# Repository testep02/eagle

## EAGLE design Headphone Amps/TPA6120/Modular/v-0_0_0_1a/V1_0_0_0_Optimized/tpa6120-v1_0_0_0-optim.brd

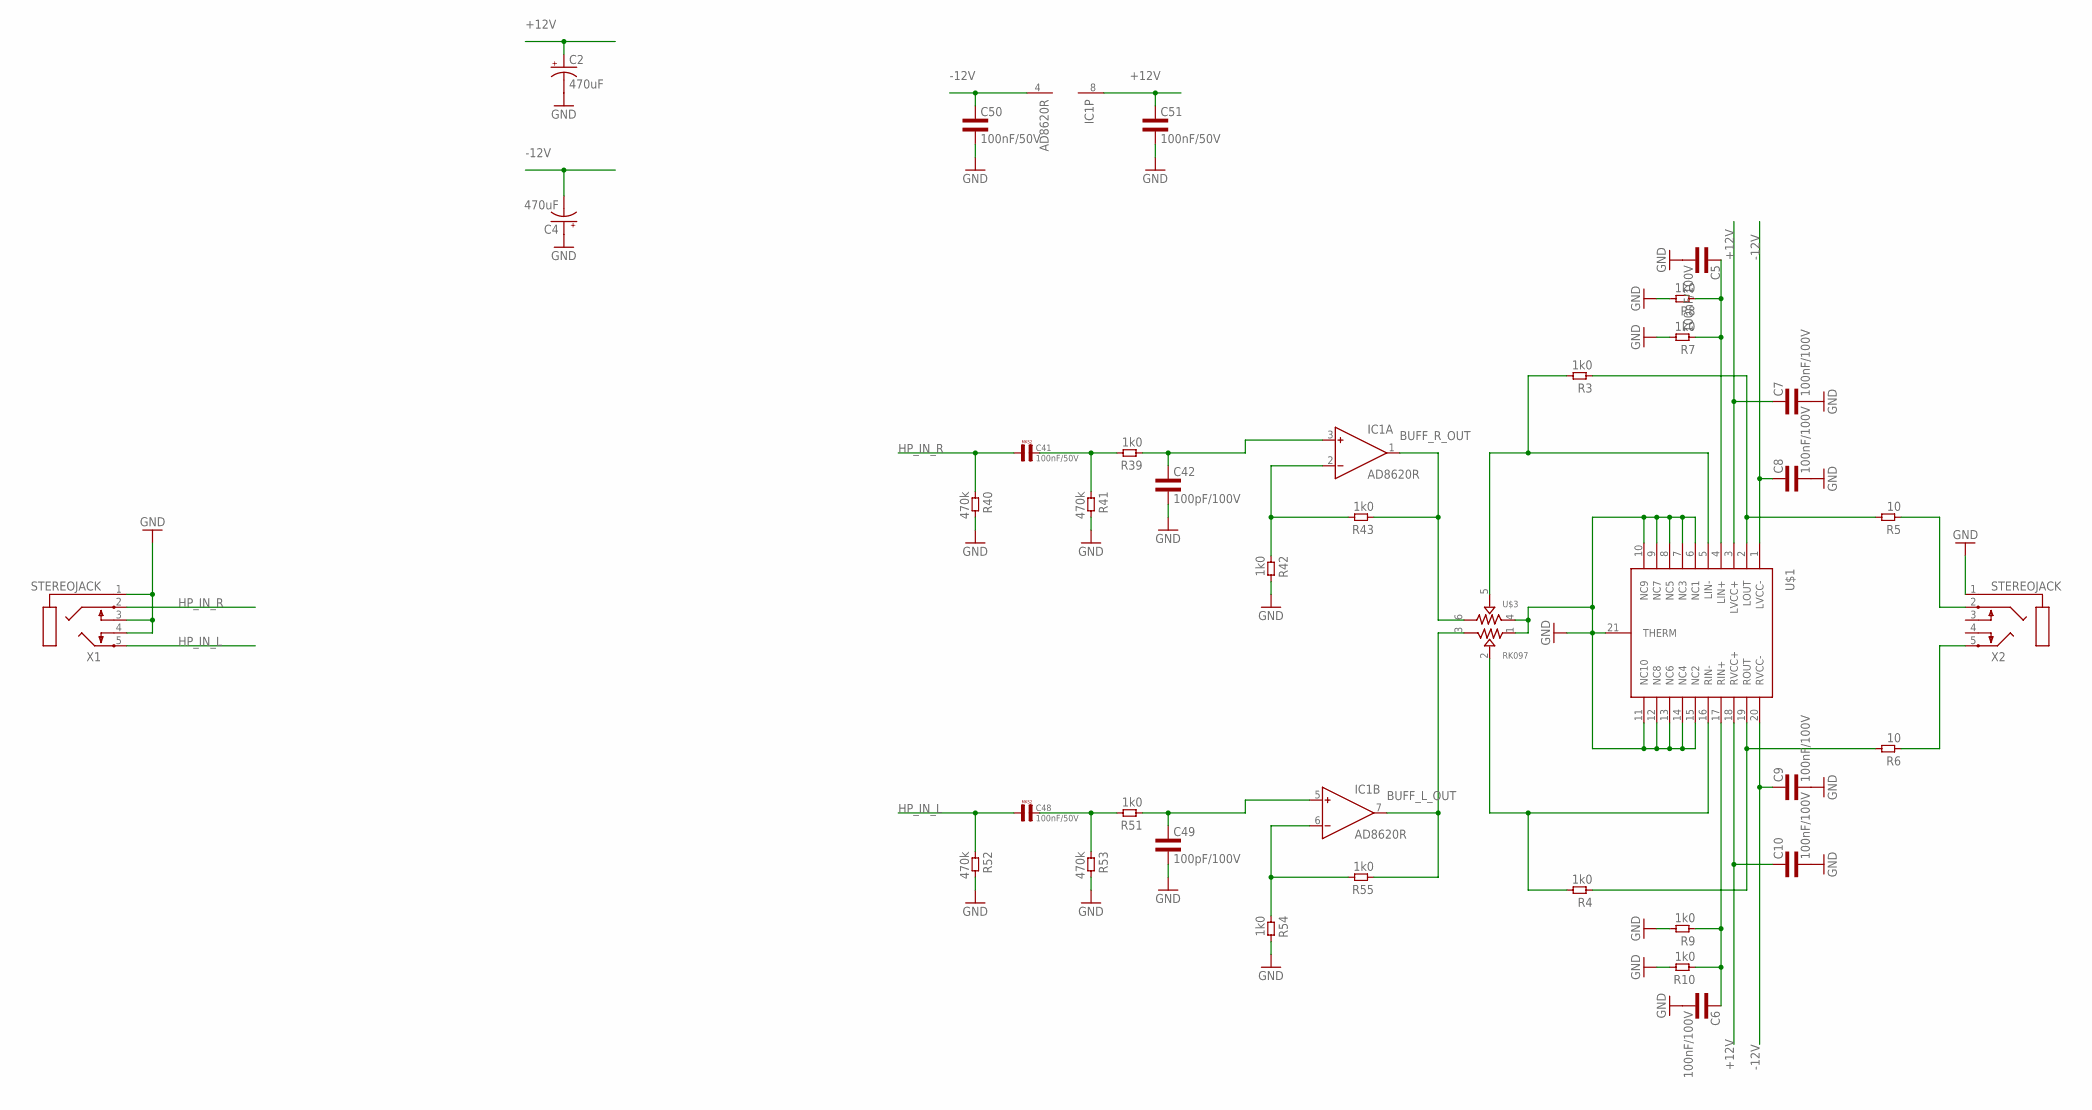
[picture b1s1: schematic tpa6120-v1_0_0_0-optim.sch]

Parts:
C2, C4: 470uF; E5-10,5
C5, C6, C7, C8, C9, C10: 100nF/100V; 0603L3
C41, C48: 100nF/50V; R5B2K5
C42, C49: 100pF/100V; 0603L3
C50, C51: 100nF/50V; 0603L3
IC1: AD8620R; SO8
R3, R4, R7, R8, R9, R10, R39, R42, R43, R51, R54, R55: 1k0; 0603L3
R5, R6: 10; 1206L3
R40, R41, R52, R53: 470k; 0603L3
U$1: TPA6120_TPA6120
U$3: RK097
X1, X2: STEREOJACK; STX3100

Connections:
+12V: C2.+, C7.P$1 (1), C10.P$1 (1), C51.P$1 (1), IC1.8 (V+), U$1.3 (LVCC+), U$1.18 (RVCC+)
-12V: C4.-, C8.P$1 (1), C9.P$1 (1), C50.P$1 (1), IC1.4 (V-), U$1.1 (LVCC-), U$1.20 (RVCC-)
BUFF_L_OUT: IC1.7 (OUT), R55.P$1 (1), U$3.3
BUFF_R_OUT: IC1.1 (OUT), R43.P$1 (1), U$3.6
GND: C2.-, C4.+, C5.P$2 (2), C6.P$2 (2), C7.P$2 (2), C8.P$2 (2), C9.P$2 (2), C10.P$2 (2), C42.P$2 (2), C49.P$2 (2), C50.P$2 (2), C51.P$2 (2), R7.P$2 (2), R8.P$2 (2), R9.P$2 (2), R10.P$2 (2), R40.P$2 (2), R41.P$2 (2), R42.P$2 (2), R52.P$2 (2), R53.P$2 (2), R54.P$2 (2), U$1.6 (NC1), U$1.7 (NC3), U$1.8 (NC5), U$1.9 (NC7), U$1.10 (NC9), U$1.11 (NC10), U$1.12 (NC8), U$1.13 (NC6), U$1.14 (NC4), U$1.15 (NC2), U$1.21 (THERM), U$3.1, U$3.4, X1.1, X1.3, X1.4, X2.1
HP_IN_L: C48.1, R52.P$1 (1), X1.5
HP_IN_R: C41.1, R40.P$1 (1), X1.2
HP_OUT_L: R6.1, X2.5
HP_OUT_R: R5.1, X2.2
INVERT_L: R3.P$2 (2), U$1.5 (LIN-), U$3.5
INVERT_R: R4.P$2 (2), U$1.16 (RIN-), U$3.2
unnamed: C5.P$1 (1), R7.P$1 (1), R8.P$1 (1), U$1.4 (LIN+)
unnamed: C6.P$1 (1), R9.P$1 (1), R10.P$1 (1), U$1.17 (RIN+)
unnamed: C41.2, R39.P$2 (2), R41.P$1 (1)
unnamed: C42.P$1 (1), IC1.3 (IN+), R39.P$1 (1)
unnamed: IC1.2 (IN-), R42.P$1 (1), R43.P$2 (2)
unnamed: C48.2, R51.P$2 (2), R53.P$1 (1)
unnamed: C49.P$1 (1), IC1.5 (IN+), R51.P$1 (1)
unnamed: IC1.6 (IN-), R54.P$1 (1), R55.P$2 (2)
OUT_L: R4.P$1 (1), R6.2, U$1.19 (ROUT)
OUT_R: R3.P$1 (1), R5.2, U$1.2 (LOUT)

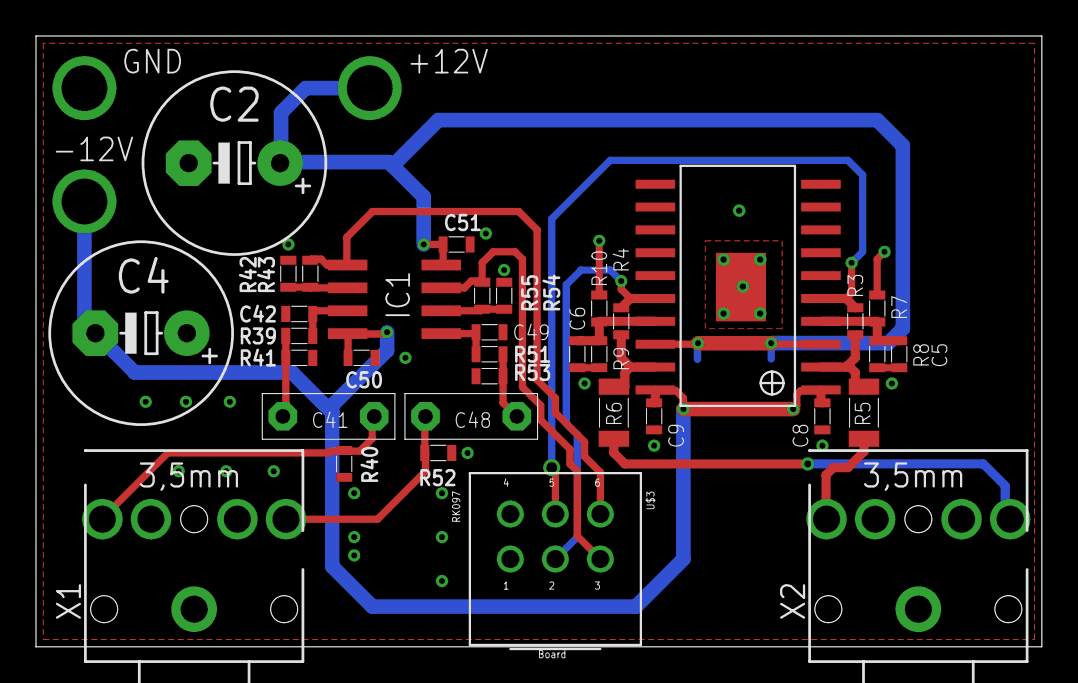
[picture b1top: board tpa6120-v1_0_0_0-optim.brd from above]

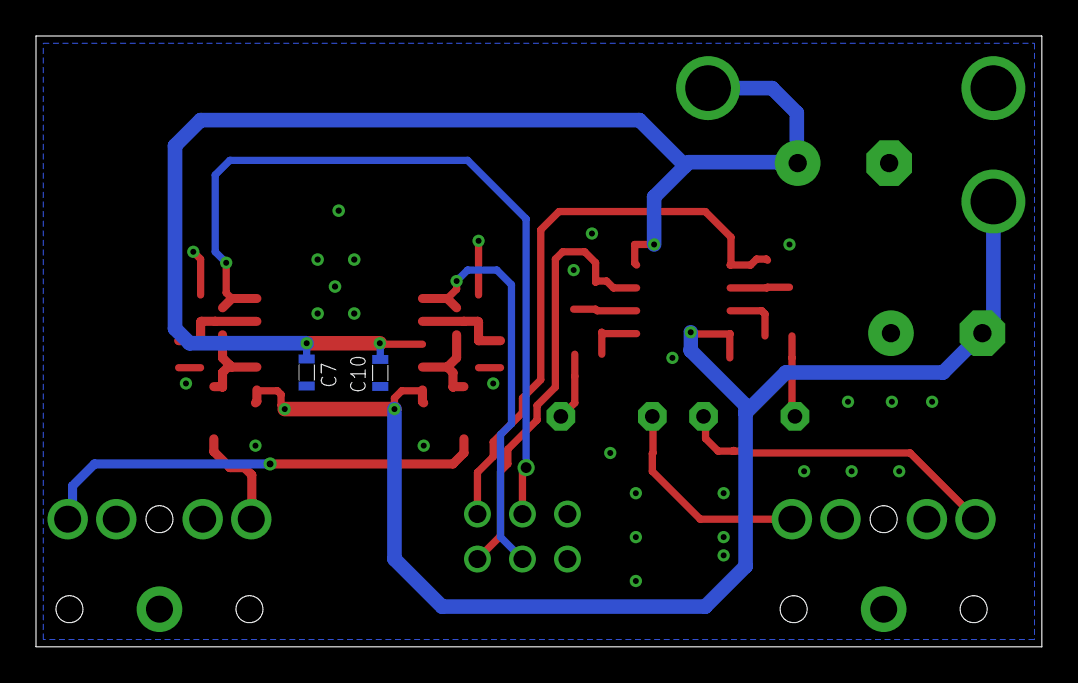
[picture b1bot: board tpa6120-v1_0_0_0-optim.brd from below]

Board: 2 copper layers, 55.9 x 33.9 mm, 37 parts (2 on the bottom side), 21 nets.

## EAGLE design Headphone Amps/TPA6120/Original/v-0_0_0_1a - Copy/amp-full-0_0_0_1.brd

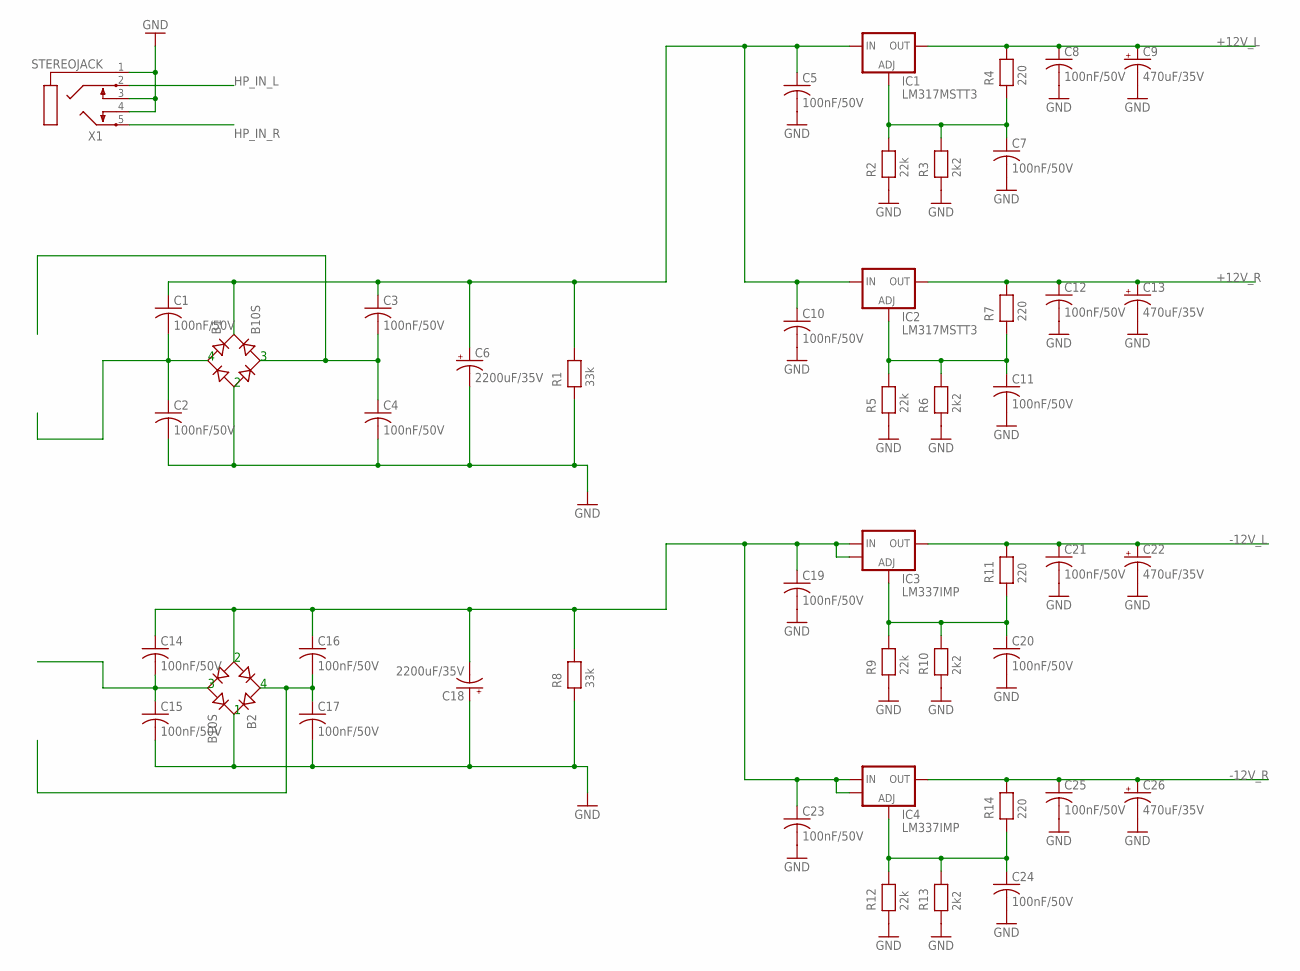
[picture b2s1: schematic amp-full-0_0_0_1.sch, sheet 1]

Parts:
B1, B2: B10S; MBS
C1, C2, C3, C4, C5, C7, C8, C10, C11, C12, C14, C15, C16, C17, C19, C20, C21, C23, C24, C25: 100nF/50V; C0805
C6, C18: 2200uF/35V; E7,5-16
C9, C13, C22, C26: 470uF/35V; E3,5-10
IC1, IC2: LM317MSTT3; SOT223
IC3, IC4: LM337IMP; SOT-223
R1, R8: 33k; R0805
R2, R5, R9, R12: 22k; R0805
R3, R6, R10, R13: 2k2; R0805
R4, R7, R11, R14: 220; R0805
X1: STEREOJACK; STX3100

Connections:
+12V_L: C8.1, C9.+, IC1.4 (OUT), R4.P$2; also elsewhere on the board
+12V_R: C12.1, C13.+, IC2.4 (OUT), R7.P$2; also elsewhere on the board
+VSS_NOREG: B1.+, C1.1, C3.1, C5.1, C6.+, C10.1, IC1.3 (IN), IC2.3 (IN), R1.P$2
-12V_L: C21.1, C22.+, IC3.3 (OUT), R11.P$2; also elsewhere on the board
-12V_R: C25.1, C26.+, IC4.3 (OUT), R14.P$2; also elsewhere on the board
-VSS_NOREG: B2.-, C14.1, C16.1, C18.-, C19.1, C23.1, IC3.2 (IN), IC3.4, IC4.2 (IN), IC4.4, R8.P$2
GND: B1.-, B2.+, C2.2, C4.2, C5.2, C6.-, C7.2, C8.2, C9.-, C10.2, C11.2, C12.2, C13.-, C15.2, C17.2, C18.+, C19.2, C20.2, C21.2, C22.-, C23.2, C24.2, C25.2, C26.-, R1.P$1, R2.P$1, R3.P$1, R5.P$1, R6.P$1, R8.P$1, R9.P$1, R10.P$1, R12.P$1, R13.P$1, X1.1, X1.3, X1.4; also elsewhere on the board
HP_IN_L: X1.2; also elsewhere on the board
HP_IN_R: X1.5; also elsewhere on the board
unnamed: B1.AC1, C1.2, C2.1
unnamed: B1.AC2, C3.2, C4.1
unnamed: B2.AC2, C14.2, C15.1
unnamed: C7.1, IC1.1 (ADJ), R2.P$2, R3.P$2, R4.P$1
unnamed: C11.1, IC2.1 (ADJ), R5.P$2, R6.P$2, R7.P$1
unnamed: B2.AC1, C16.2, C17.1
unnamed: C20.1, IC3.1 (ADJ), R9.P$2, R10.P$2, R11.P$1
unnamed: C24.1, IC4.1 (ADJ), R12.P$2, R13.P$2, R14.P$1

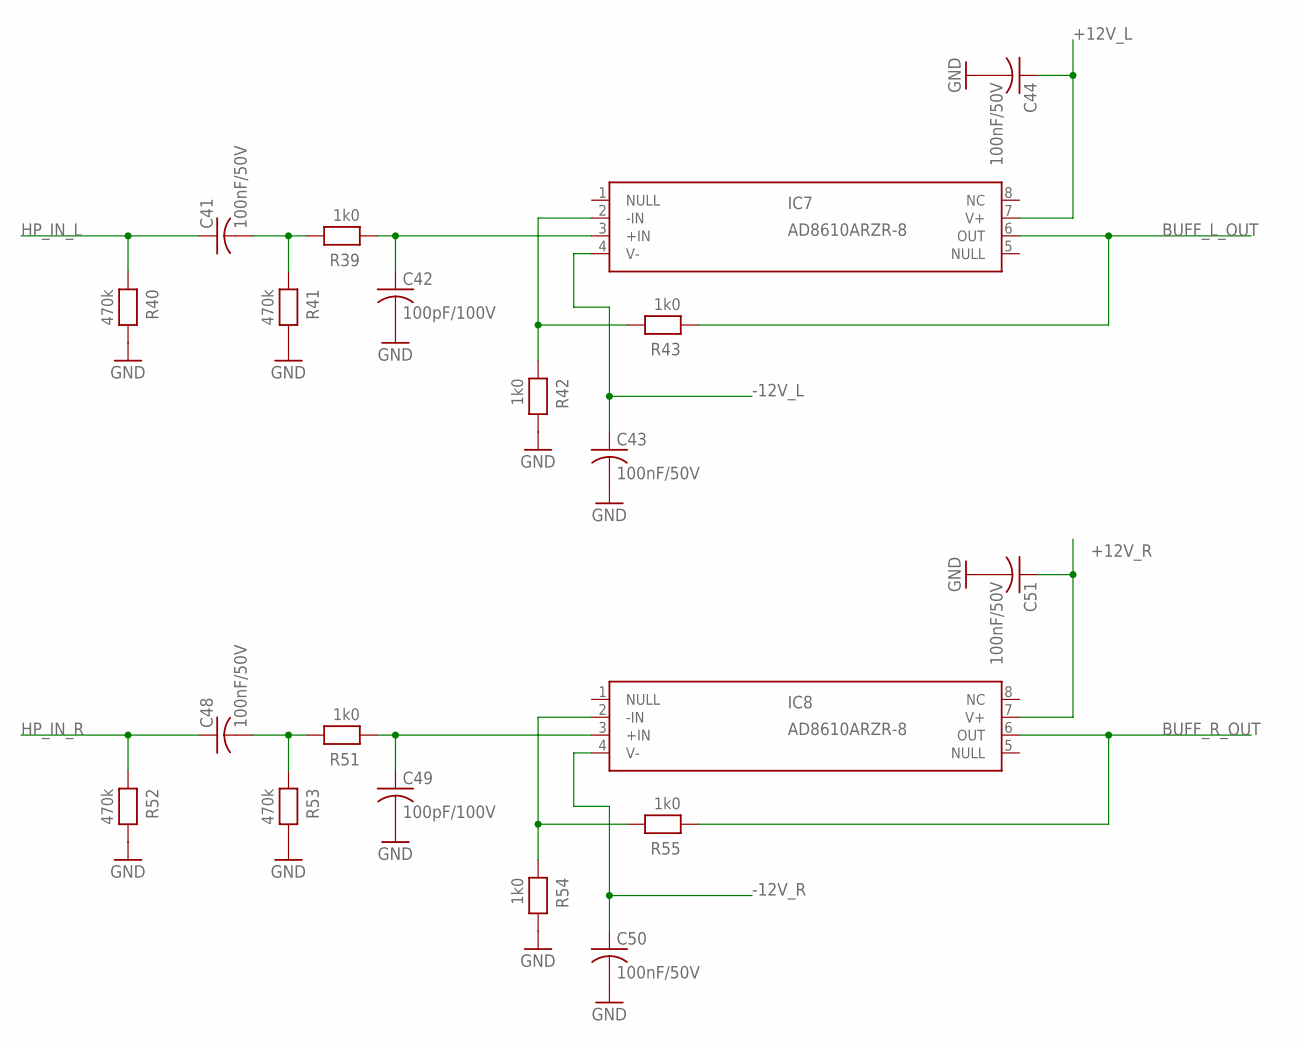
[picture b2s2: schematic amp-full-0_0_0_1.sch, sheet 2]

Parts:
C41, C43, C44, C48, C50, C51: 100nF/50V; C0805
C42, C49: 100pF/100V; C0805
IC7, IC8: AD8610ARZR-8; 8-LEAD-SOIC_N
R39, R42, R43, R51, R54, R55: 1k0; R0805
R40, R41, R52, R53: 470k; R0805

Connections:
+12V_L: C44.1, IC7.7 (V+); also elsewhere on the board
+12V_R: C51.1, IC8.7 (V+); also elsewhere on the board
-12V_L: C43.1, IC7.4 (V-); also elsewhere on the board
-12V_R: C50.1, IC8.4 (V-); also elsewhere on the board
BUFF_L_OUT: IC7.6 (OUT), R43.P$1; also elsewhere on the board
BUFF_R_OUT: IC8.6 (OUT), R55.P$1; also elsewhere on the board
GND: C42.2, C43.2, C44.2, C49.2, C50.2, C51.2, R40.P$2, R41.P$2, R42.P$2, R52.P$2, R53.P$2, R54.P$2; also elsewhere on the board
HP_IN_L: C41.1, R40.P$1; also elsewhere on the board
HP_IN_R: C48.1, R52.P$1; also elsewhere on the board
unnamed: C41.2, R39.P$2, R41.P$1
unnamed: C42.1, IC7.3 (+IN), R39.P$1
unnamed: IC7.2 (-IN), R42.P$1, R43.P$2
unnamed: C48.2, R51.P$2, R53.P$1
unnamed: C49.1, IC8.3 (+IN), R51.P$1
unnamed: IC8.2 (-IN), R54.P$1, R55.P$2

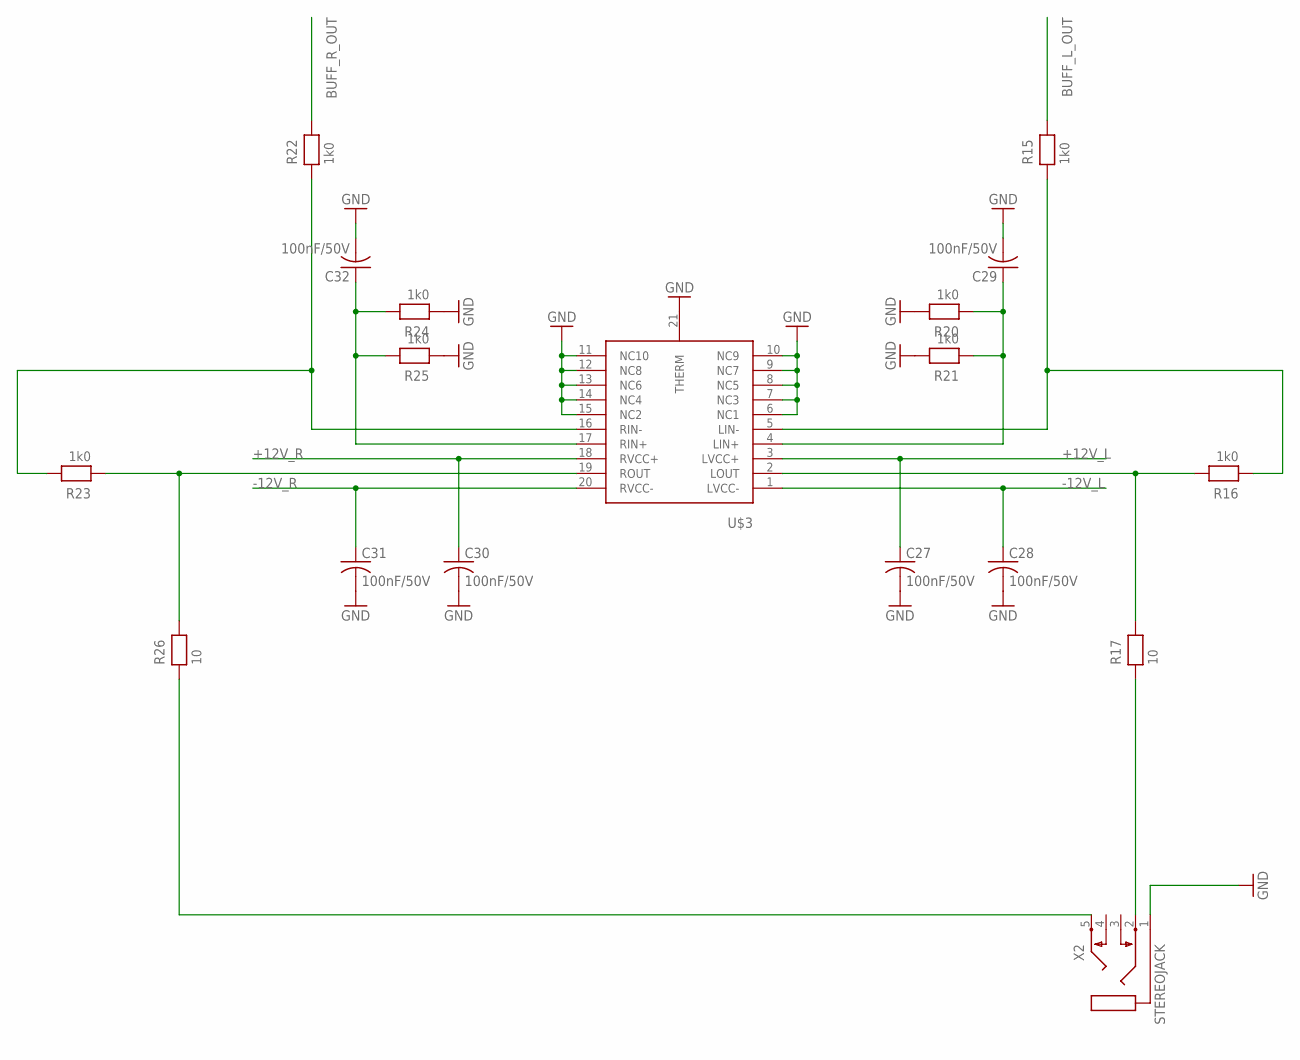
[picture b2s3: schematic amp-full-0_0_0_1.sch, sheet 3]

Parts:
C27, C28, C29, C30, C31, C32: 100nF/50V; C0805
R15, R16, R20, R21, R22, R23, R24, R25: 1k0; R0805
R17, R26: 10; R0805
U$3: TPA6120
X2: STEREOJACK; STX3100

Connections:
+12V_L: C27.1, U$3.3 (LVCC+); also elsewhere on the board
+12V_R: C30.1, U$3.18 (RVCC+); also elsewhere on the board
-12V_L: C28.1, U$3.1 (LVCC-); also elsewhere on the board
-12V_R: C31.1, U$3.20 (RVCC-); also elsewhere on the board
BUFF_L_OUT: R15.P$2; also elsewhere on the board
BUFF_R_OUT: R22.P$2; also elsewhere on the board
GND: C27.2, C28.2, C29.2, C30.2, C31.2, C32.2, R20.P$2, R21.P$2, R24.P$1, R25.P$1, U$3.6 (NC1), U$3.7 (NC3), U$3.8 (NC5), U$3.9 (NC7), U$3.10 (NC9), U$3.11 (NC10), U$3.12 (NC8), U$3.13 (NC6), U$3.14 (NC4), U$3.15 (NC2), U$3.21 (THERM), X2.1; also elsewhere on the board
unnamed: R15.P$1, R16.P$1, U$3.5 (LIN-)
unnamed: R16.P$2, R17.P$2, U$3.2 (LOUT)
unnamed: R17.P$1, X2.2
unnamed: C29.1, R20.P$1, R21.P$1, U$3.4 (LIN+)
unnamed: R22.P$1, R23.P$2, U$3.16 (RIN-)
unnamed: R23.P$1, R26.P$2, U$3.19 (ROUT)
unnamed: C32.1, R24.P$2, R25.P$2, U$3.17 (RIN+)
unnamed: R26.P$1, X2.5

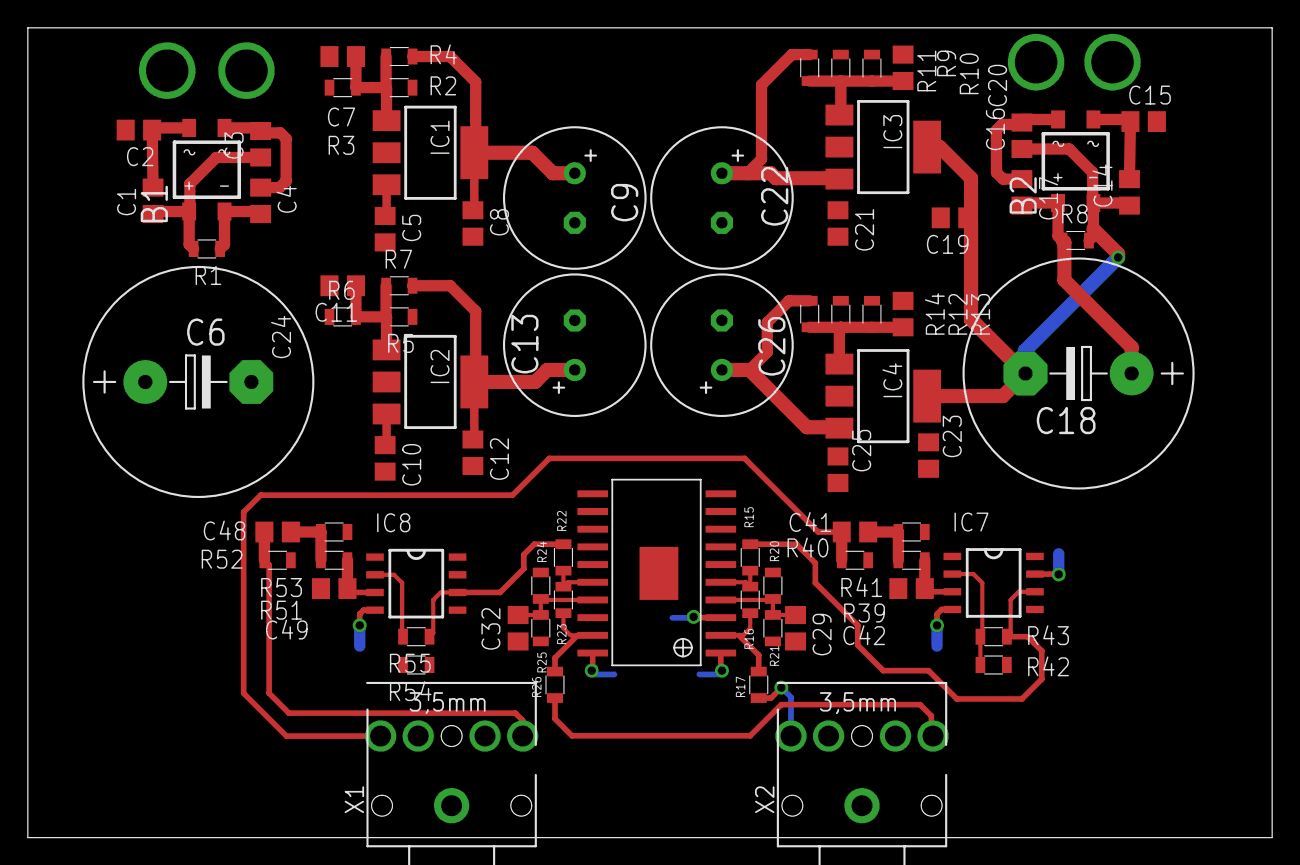
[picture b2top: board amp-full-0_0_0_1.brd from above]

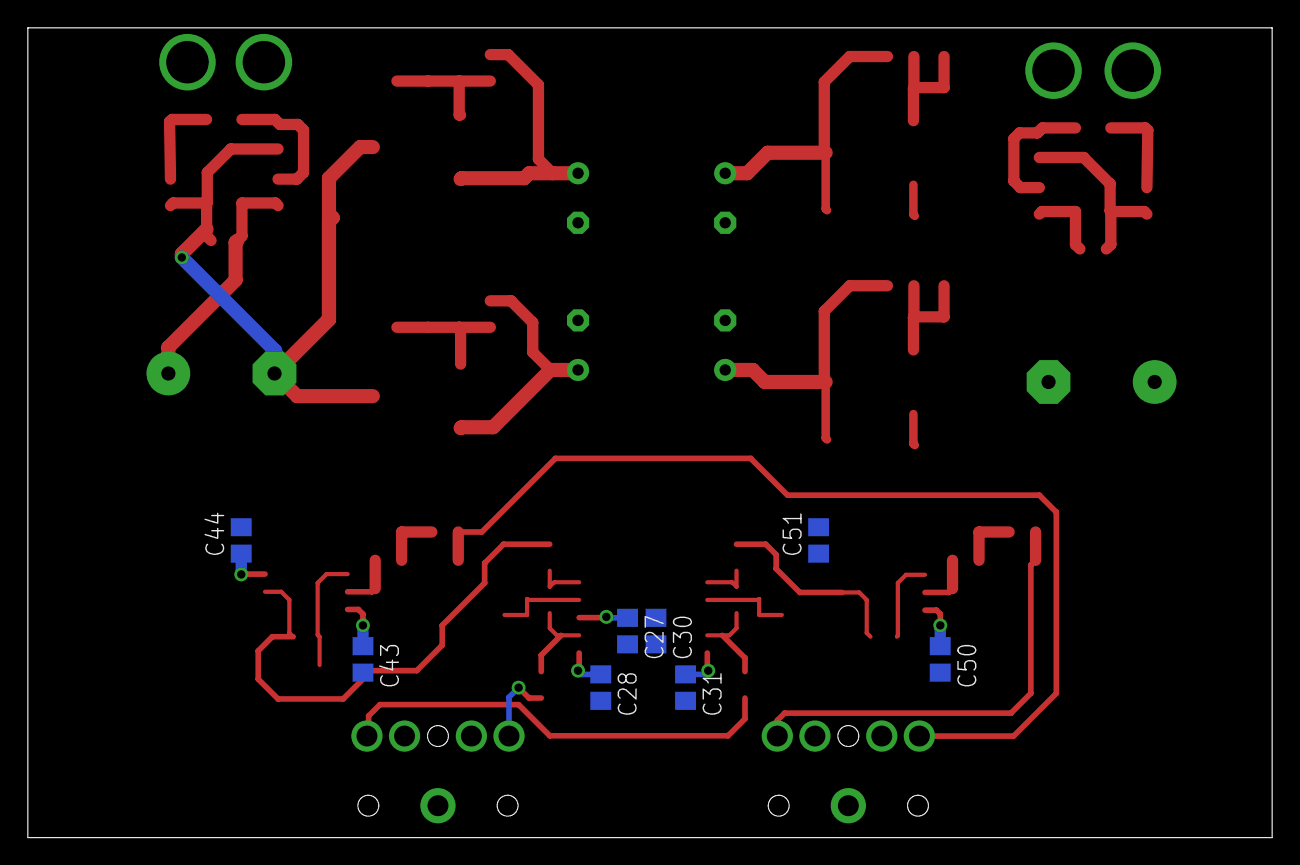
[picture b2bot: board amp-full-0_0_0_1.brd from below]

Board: 2 copper layers, 89.3 x 58.1 mm, 85 parts (8 on the bottom side), 33 nets.

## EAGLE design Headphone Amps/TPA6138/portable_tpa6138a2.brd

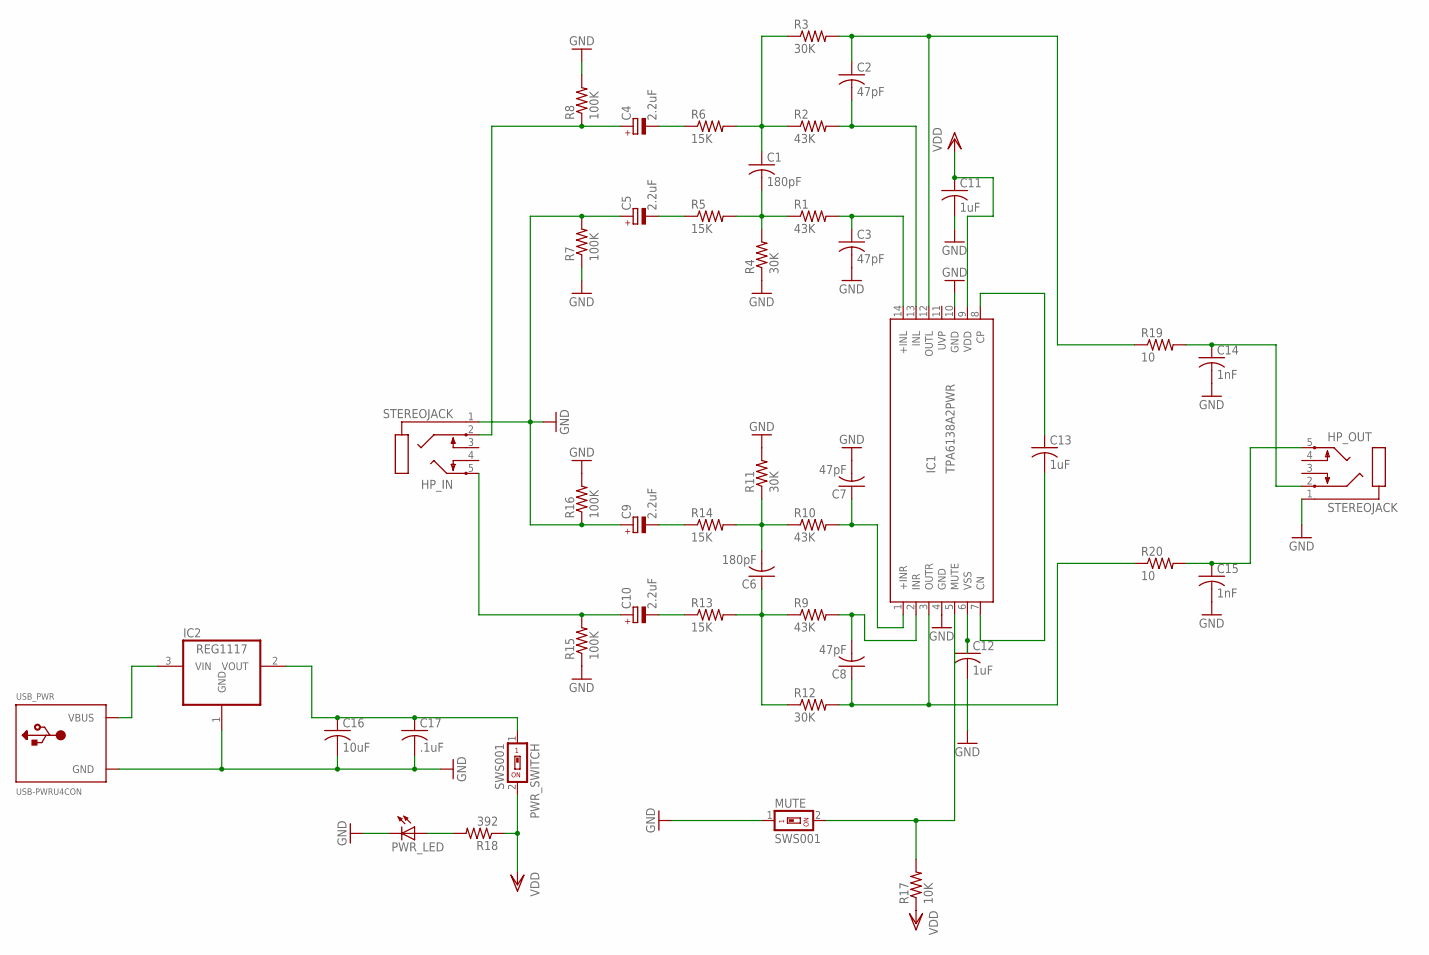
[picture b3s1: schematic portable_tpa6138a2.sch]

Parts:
C1, C6: 180pF; C0603
C2, C3, C7, C8: 47pF; C0603
C4, C5, C9, C10: 2.2uF; 153CLV-0405
C11, C12, C13: 1uF; C0603
C14, C15: 1nF; C0603
C16: 10uF; C0805
C17: .1uF; C0603
HP_IN: STEREOJACK; STX3100
HP_OUT: STEREOJACK; STX3100
IC1: TPA6138A2PWR; TSSOP14
IC2: REG1117; SOT223
MUTE: SWS001; SMS-001
PWR_LED: LED; SMARTLED-TTW
PWR_SWITCH: SWS001; SMS-001
R1, R2, R9, R10: 43K; R0603
R3, R4, R11, R12: 30K; R0603
R5, R6, R13, R14: 15K; R0603
R7, R8, R15, R16: 100K; R0603
R17: 10K; R0603
R18: 392; R0603
R19, R20: 10; R0603
USB_PWR: USB-PWRU4CON; USB-MINIB-THM-PWRONLY

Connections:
GND: C3.2, C5.+, C7.2, C9.+, C11.2, C12.2, C14.2, C15.2, C16.2, C17.2, HP_IN.1, HP_OUT.1, IC1.4 (GND), IC1.10 (GND), IC2.1 (GND), MUTE.1, PWR_LED.C@1 (C), R4.1, R7.1, R7.2, R8.2, R11.2, R15.1, R16.1, R16.2, USB_PWR.GND
unnamed: IC2.3 (VIN), USB_PWR.VBUS
unnamed: PWR_LED.A@1 (A), R18.2
unnamed: C4.+, HP_IN.2, R8.1
unnamed: C4.-, R6.1
unnamed: C1.1, R2.1, R3.1, R6.2
unnamed: C10.+, HP_IN.5, R15.2
unnamed: C5.-, R5.1
unnamed: C1.2, R1.1, R4.2, R5.2
unnamed: C2.2, IC1.13 (INL), R2.2
unnamed: C2.1, IC1.12 (OUTL), R3.2, R19.1
unnamed: C6.2, R10.1, R11.1, R14.2
unnamed: C7.1, IC1.1 (+INR), R10.2
unnamed: C3.1, IC1.14 (+INL), R1.2
unnamed: C10.-, R13.1
unnamed: C6.1, R9.1, R12.1, R13.2
unnamed: C8.2, IC1.2 (INR), R9.2
unnamed: C8.1, IC1.3 (OUTR), R12.2, R20.1
unnamed: C13.2, IC1.7 (CN)
unnamed: C13.1, IC1.8 (CP)
unnamed: C12.1, IC1.6 (VSS)
unnamed: C14.1, HP_OUT.2, R19.2
unnamed: C15.1, HP_OUT.5, R20.2
unnamed: C9.-, R14.1
unnamed: IC1.5 (MUTE), MUTE.2, R17.2
unnamed: C16.1, C17.1, IC2.2 (VOUT), PWR_SWITCH.1
VDD: C11.1, IC1.9 (VDD), PWR_SWITCH.2, R17.1, R18.1

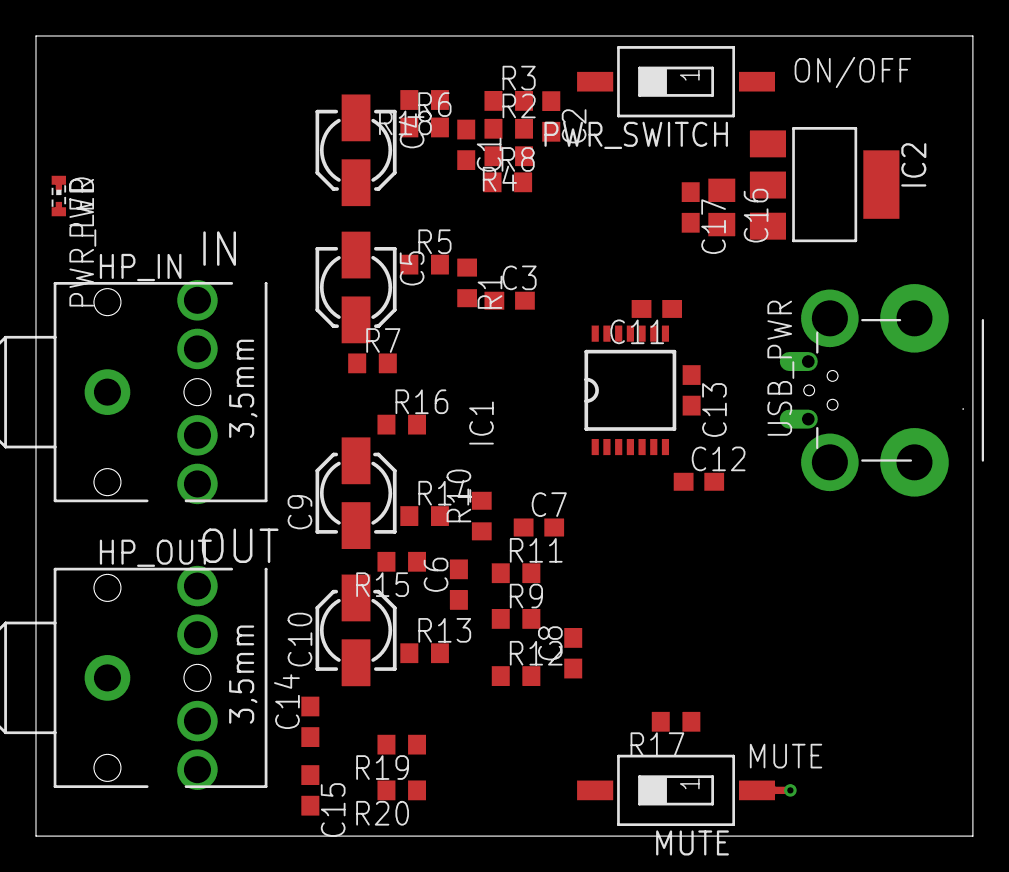
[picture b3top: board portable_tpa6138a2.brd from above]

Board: 2 copper layers, 52.0 x 44.5 mm, 45 parts (0 on the bottom side), 27 nets.

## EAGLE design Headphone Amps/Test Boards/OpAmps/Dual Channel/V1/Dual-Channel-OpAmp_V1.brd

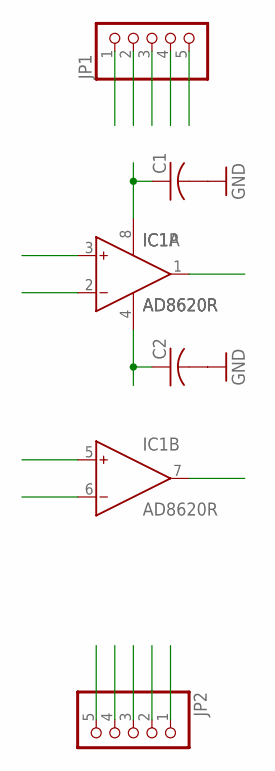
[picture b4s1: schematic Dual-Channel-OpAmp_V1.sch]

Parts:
C1, C2: C-USC0805; C0805
IC1: AD8620R; SO8
JP1, JP2: PINHD-1X5; 1X05

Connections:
1: IC1.1 (OUT), JP1.1
2: IC1.2 (IN-), JP1.2
3: IC1.3 (IN+), JP1.3
4: C2.1, IC1.4 (V-), JP1.4
5: IC1.5 (IN+), JP2.4
6: IC1.6 (IN-), JP2.3
7: IC1.7 (OUT), JP2.2
8: C1.1, IC1.8 (V+), JP2.1
GND: C1.2, C2.2, JP1.5, JP2.5

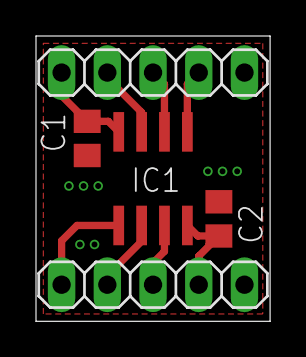
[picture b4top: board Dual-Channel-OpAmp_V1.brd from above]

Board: 2 copper layers, 13.0 x 15.8 mm, 5 parts (0 on the bottom side), 9 nets.

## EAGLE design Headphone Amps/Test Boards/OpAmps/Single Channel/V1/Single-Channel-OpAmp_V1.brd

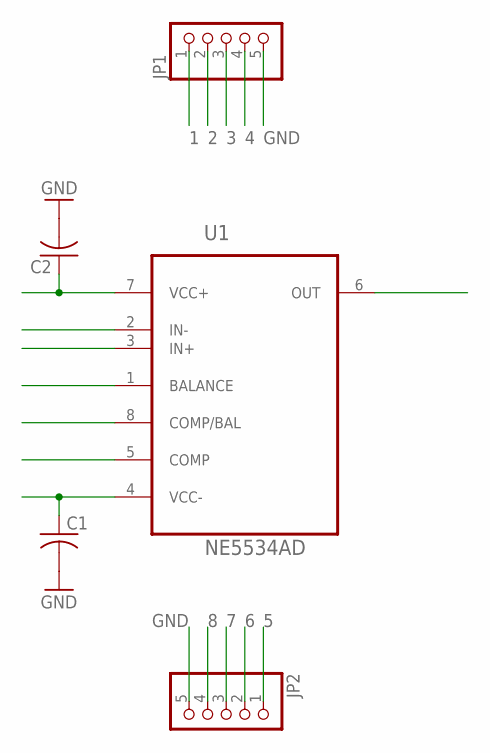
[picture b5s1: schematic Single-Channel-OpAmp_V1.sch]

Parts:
C1, C2: C-USC0805; C0805
JP1, JP2: PINHD-1X5; 1X05
U1: NE5534AD; SOIC127P600X175-8N

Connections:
1: JP1.1, U1.1 (BALANCE)
2: JP1.2, U1.2 (IN-)
3: JP1.3, U1.3 (IN+)
4: C1.1, JP1.4, U1.4 (VCC-)
5: JP2.1, U1.5 (COMP)
6: JP2.2, U1.6 (OUT)
7: C2.1, JP2.3, U1.7 (VCC+)
8: JP2.4, U1.8 (COMP/BAL)
GND: C1.2, C2.2, JP1.5, JP2.5

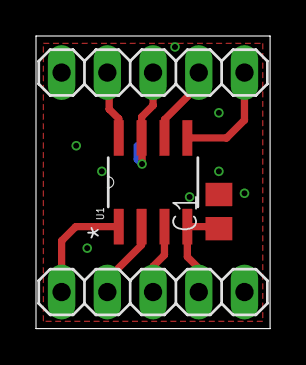
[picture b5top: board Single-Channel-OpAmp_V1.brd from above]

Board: 2 copper layers, 13.0 x 16.3 mm, 5 parts (1 on the bottom side), 9 nets.

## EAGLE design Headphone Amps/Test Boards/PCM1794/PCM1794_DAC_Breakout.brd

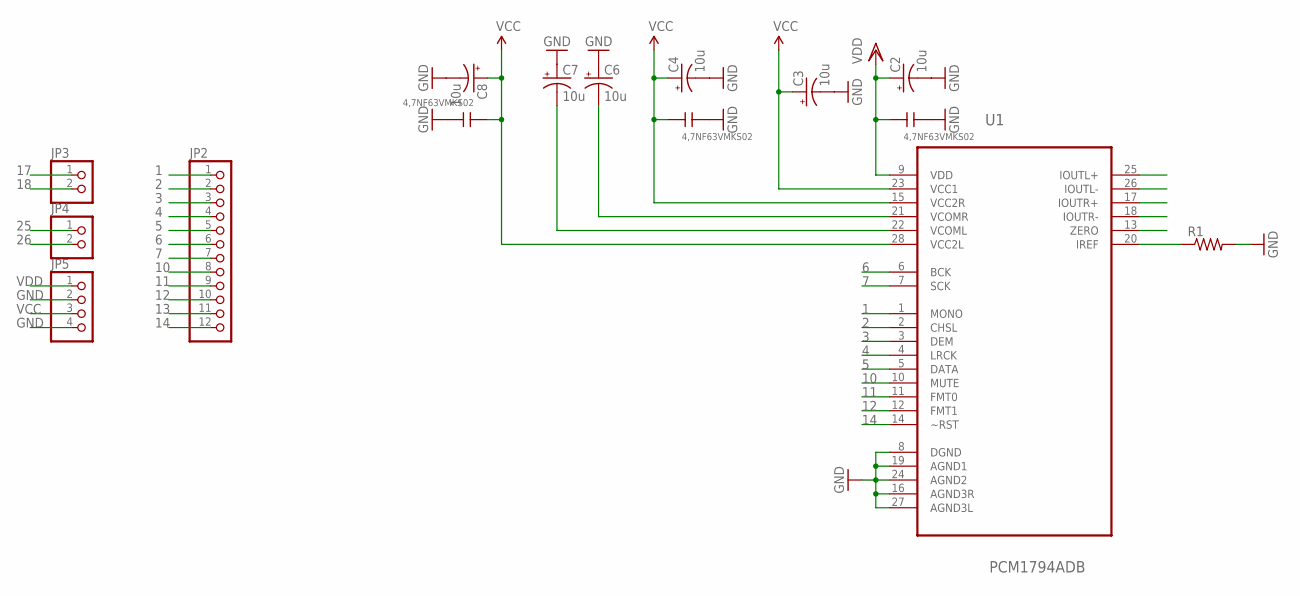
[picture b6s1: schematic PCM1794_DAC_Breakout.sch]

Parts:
C1, C5, C9: 4,7NF63VMKS02; 2,5X7,0RM2,5
C2, C3, C4, C6, C7, C8: 10u; E2,5-6
JP2: PINHD-1X12; 1X12
JP3, JP4: PINHD-1X2; 1X02
JP5: PINHD-1X4; 1X04
R1: R-US_R0603; R0603
U1: PCM1794ADB; SOP65P780X200-28N

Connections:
1: JP2.1, U1.1 (MONO)
2: JP2.2, U1.2 (CHSL)
3: JP2.3, U1.3 (DEM)
4: JP2.4, U1.4 (LRCK)
5: JP2.5, U1.5 (DATA)
6: JP2.6, U1.6 (BCK)
7: JP2.7, U1.7 (SCK)
10: JP2.8, U1.10 (MUTE)
11: JP2.9, U1.11 (FMT0)
12: JP2.10, U1.12 (FMT1)
13: JP2.11, U1.13 (ZERO)
14: JP2.12, U1.14 (~RST)
17: JP3.1, U1.17 (IOUTR+)
18: JP3.2, U1.18 (IOUTR-)
20: R1.1, U1.20 (IREF)
25: JP4.1, U1.25 (IOUTL+)
26: JP4.2, U1.26 (IOUTL-)
GND: C1.2, C2.-, C3.-, C4.-, C5.2, C6.+, C7.+, C8.-, C9.2, JP5.2, JP5.4, R1.2, U1.8 (DGND), U1.16 (AGND3R), U1.19 (AGND1), U1.24 (AGND2), U1.27 (AGND3L)
unnamed: C6.-, U1.21 (VCOMR)
unnamed: C7.-, U1.22 (VCOML)
VCC: C3.+, C4.+, C5.1, C8.+, C9.1, JP5.3, U1.15 (VCC2R), U1.23 (VCC1), U1.28 (VCC2L)
VDD: C1.1, C2.+, JP5.1, U1.9 (VDD)

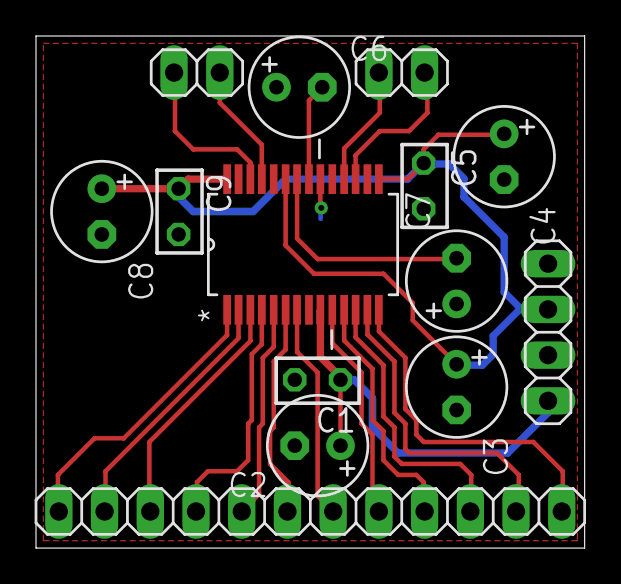
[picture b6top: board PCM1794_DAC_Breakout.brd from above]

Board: 2 copper layers, 30.5 x 28.4 mm, 15 parts (1 on the bottom side), 22 nets.

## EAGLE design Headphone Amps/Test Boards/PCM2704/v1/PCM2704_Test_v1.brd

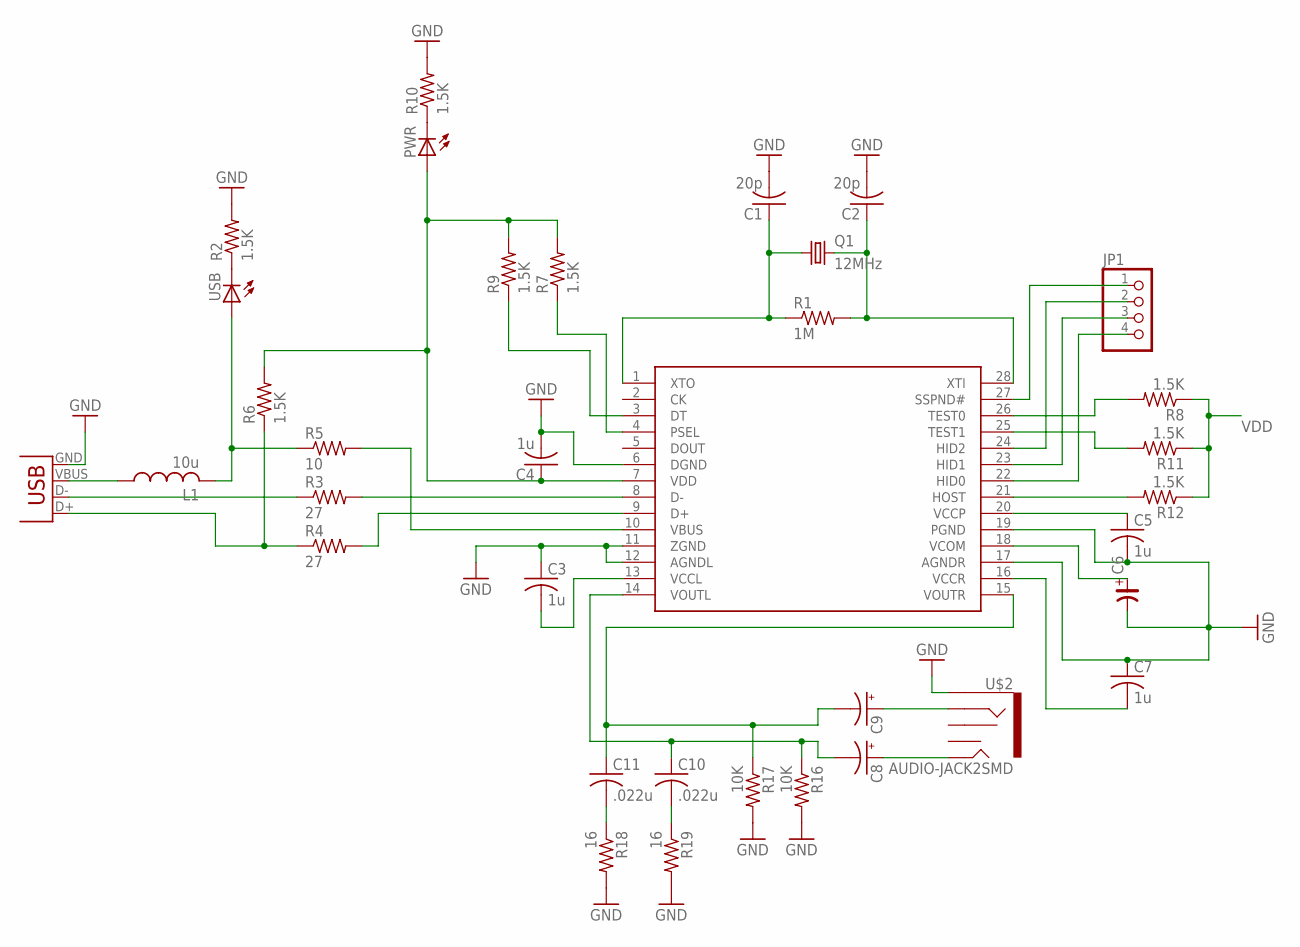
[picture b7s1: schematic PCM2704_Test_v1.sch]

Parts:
C1, C2: 20p; C0603
C3, C4, C5, C7: 1u; C0603
C6: CP_E-010X030; CE-010X030
C8, C9: CPOL-USE1.8-4; E1,8-4
C10, C11: .022u; C0603
JP1: PINHD-1X4; 1X04
L1: 10u; L3225M
PWR: LEDCHIP-LED0603; CHIP-LED0603
Q1: 12MHz; HC49US
R1: 1M; R0603
R2, R6, R7, R8, R9, R10, R11, R12: 1.5K; R0603
R3, R4: 27; R0603
R5: 10; R0603
R16, R17: 10K; R0603
R18, R19: 16; R0603
U$1: PCM2704C
U$2: AUDIO-JACK2SMD; AUDIO-JACK-3.5MM-SMD
USB: LEDCHIP-LED0603; CHIP-LED0603
X1: USB-MB-S

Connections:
GND: C1.2, C2.2, C3.1, C4.2, C5.2, C6.-, C7.1, R2.2, R10.2, R16.2, R17.2, R18.2, R19.2, U$1.6 (DGND), U$1.11 (ZGND), U$1.12 (AGNDL), U$1.17 (AGNDR), U$1.19 (PGND), U$2.SLEEVE, X1.GND
unnamed: C1.1, Q1.1, R1.1, U$1.1 (XTO)
unnamed: C2.1, Q1.2, R1.2, U$1.28 (XTI)
unnamed: R3.2, U$1.8 (D-)
unnamed: C3.2, U$1.13 (VCCL)
unnamed: R8.2, U$1.26 (TEST0)
unnamed: R4.2, U$1.9 (D+)
unnamed: L1.2, R5.1, USB.A
unnamed: R5.2, U$1.10 (VBUS)
unnamed: R11.2, U$1.25 (TEST1)
unnamed: C9.-, C11.1, R17.1, U$1.15 (VOUTR)
unnamed: R12.2, U$1.21 (HOST)
unnamed: JP1.1, U$1.27 (SSPND#)
unnamed: C5.1, U$1.20 (VCCP)
unnamed: C6.+, U$1.18 (VCOM)
unnamed: R9.1, U$1.3 (DT)
unnamed: R2.1, USB.C
unnamed: C8.+, U$2.TIP
unnamed: JP1.2, U$1.24 (HID2)
unnamed: JP1.3, U$1.23 (HID1)
unnamed: JP1.4, U$1.22 (HID0)
unnamed: PWR.C, R10.1
unnamed: C7.2, U$1.16 (VCCR)
unnamed: C8.-, C10.1, R16.1, U$1.14 (VOUTL)
unnamed: C9.+, U$2.RING
unnamed: C11.2, R18.1
unnamed: C10.2, R19.1
PSEL: R7.1, U$1.4 (PSEL)
USB_D_N: R3.1, X1.D-
USB_D_P: R4.1, R6.1, X1.D+
VBUS_RAW: L1.1, X1.VBUS
VDD: C4.1, PWR.A, R6.2, R7.2, R8.1, R9.2, R11.1, R12.1, U$1.7 (VDD)

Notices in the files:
parts and their libraries:
SparkFun-Electromechanical: Licensing: CC v3.0 Share-Alike You are welcome to use this library for commercial purposes.
rc-master: Copyright (C) 2007, Bob Starr
